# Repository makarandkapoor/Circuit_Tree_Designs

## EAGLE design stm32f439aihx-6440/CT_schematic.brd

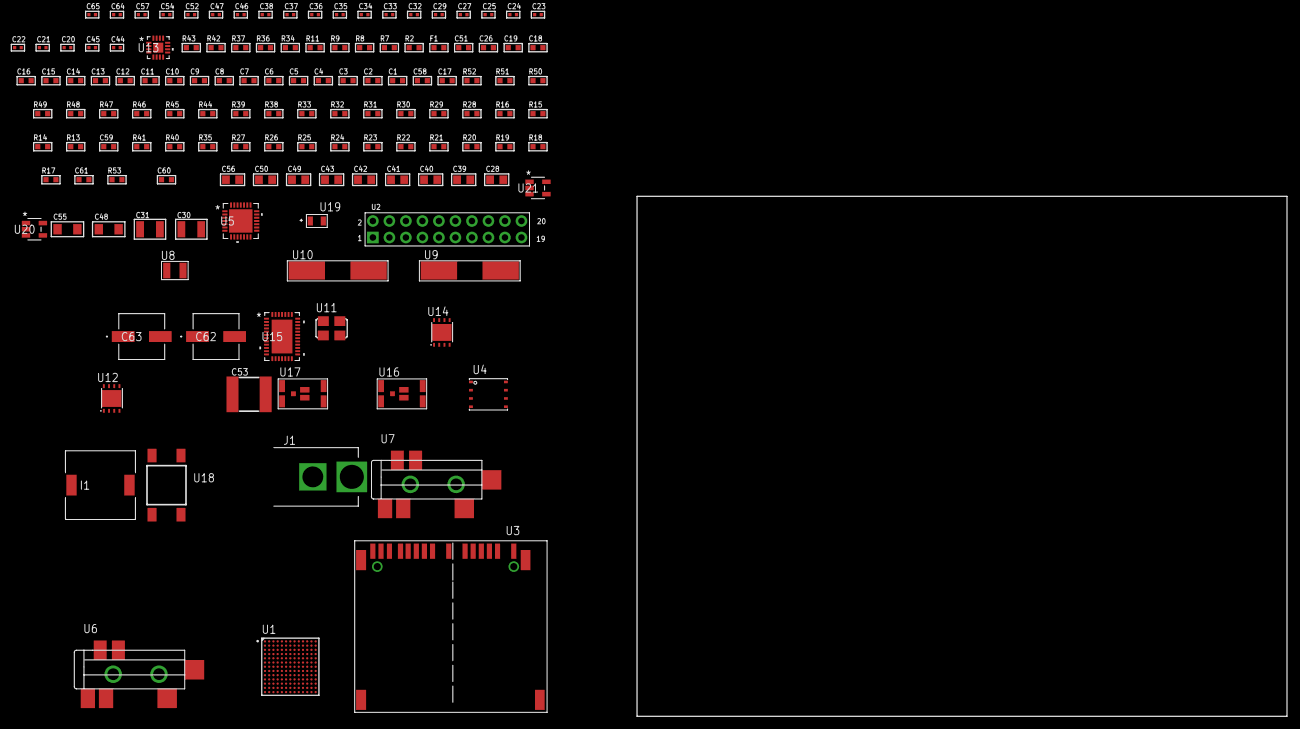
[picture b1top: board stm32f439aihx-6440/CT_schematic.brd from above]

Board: 2 copper layers, 100.0 x 80.0 mm, 135 parts (0 on the bottom side), 88 nets, no tracks yet.

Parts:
C1, C19, C26, C51: 1e-06; C0603
C2, C3, C4, C5, C6, C7, C8, C9, C10, C11, C12, C13, C14, C15, C16: 1e-07; C0603
C17: 4.7e-06; C0603
C18: 1e-08; C0603
C20, C21, C27, C34, C35, C36, C37, C38, C52, C57: 1e-07; C0402
C22, C23, C24, C25: 1e-11; C0402
C28, C39, C40, C41, C42, C43, C49, C50, C56: 1e-05; C0805
C29, C46, C47, C54, C64, C65: 1e-08; C0402
C30, C31: 2.2e-05; C1210
C32, C33: 1e-09; C0402
C44, C45: 2.2e-11; C0402
C48, C55: 1e-05; C1206
C53: 6.8e-05; 2220
C58: 2.2e-06; C0603
C59: 2.45e-08; R0603
C60: 2.8258362168397e-09; R0603
C61: 7.105e-09; R0603
C62, C63: 0.0001; EXV-9H
F1: 240.0; L0603
I1: 3.8e-06; DR1040
J1: PJ-037B; PJ-037B_PACKAGE
R2, R37, R43: 1000.0; R0603
R7, R8: 4700.0; R0603
R9, R11: 2200.0; R0603
R13, R14, R15, R16, R28, R29, R30, R44, R46, R47, R50, R51, R52: 10000.0; R0603
R17, R18, R19, R20, R21, R22, R23, R24, R25, R26, R27, R35, R41: 100000.0; R0603
R31, R32, R33: 47000.0; R0603
R34: 680.0; R0603
R36, R42: 200.0; R0603
R38: 20000.0; R0603
R39: 91000.0; R0603
R40: 300000.0; R0603
R45: 75000.0; R0603
R48, R49: 95300.0; R0603
R53: 76618.181818182; R0603
U1: STM32F439AIH6; UFBGA169
U2: arducam_ov2640; ARDUCAM
U3: 10100565
U4: 24AA256-I/MF; DFN8-S
U5: WM8731CLSEFL; QFN-28
U6, U7: SJ-43515TS-SMT-TR
U8: ABS07-32.768KHZ-7-T
U9: ABLS-25.000MHZ-B2F-T
U10: ABLS-12.288MHZ-B4-T
U11: ASFL1-25MHZ-NCS; ASFL1
U12, U14: LP3878SDX-ADJ/NOPB; WSON-8
U13: LTC3601EUD#PBF; QFN-16_EP
U15: LTC2928CUHF#PBF; QFN-38_UHF
U16, U17: IRF8306MTRPbF; IRF8306MTRPBF
U18: 4-1437565-2; SW_4-1437565-2
U19: Q65110A2395; LGM67K-G1J2-24-Z
U20, U21: nc7sz125m5x; NC7SZ125M5X

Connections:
CLK_CRYSTAL_U1_E1: C22.1, U1.E1, U8.1
CLK_CRYSTAL_U1_F1: C23.1, U1.F1, U8.2
CLK_CRYSTAL_U1_G1: C24.1, U1.G1, U9.1
CLK_CRYSTAL_U1_G2: C25.1, U1.G2, U9.2
CLK_CRYSTAL_U5_1: C44.1, U5.1, U10.1
CLK_CRYSTAL_U5_2: C45.1, U5.2, U10.2
CLK_U2_8: U2.8, U11.3
GND: C1.2, C2.2, C3.2, C4.2, C5.2, C6.2, C7.2, C8.2, C9.2, C10.2, C11.2, C12.2, C13.2, C14.2, C15.2, C16.2, C17.2, C18.2, C19.2, C20.2, C21.2, C22.2, C23.2, C24.2, C25.2, C26.2, C27.2, C28.2, C29.2, C33.2, C34.2, C35.2, C36.2, C37.2, C38.2, C39.2, C40.2, C41.2, C42.2, C43.2, C44.2, C45.2, C46.2, C47.2, C48.2, C49.2, C50.2, C51.2, C53.1, C53.2, C54.2, C55.2, C56.2, C57.2, C58.2, C59.2, C60.2, C61.2, C62.2, C63.2, C64.2, C65.2, J1.2, R2.2, R15.2, R29.2, R30.2, R31.2, R32.2, R33.2, R37.2, R38.2, R40.2, R43.2, R45.2, R48.2, R49.2, R50.2, R51.2, R52.2, U1.D7, U1.D11, U1.E7, U1.F5, U1.F6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
NET_U1_A5: R14.1, U1.A5
NET_U1_B5: R11.1, U1.B5, U4.5
NET_U1_C3: R13.1, U1.C3
NET_U1_C5: R9.1, U1.C5, U4.6
NET_U1_D12: C21.1, U1.D12
NET_U1_H2: R7.1, U1.H2, U20.4
NET_U1_J4: C18.1, C19.1, F1.1, U1.J3, U1.J4
NET_U1_L5: R15.1, U1.L5
NET_U1_M1: R16.1, U1.M1
NET_U1_N12: U18.3, U18.4
NET_U2_19: R8.1, U2.19, U21.4
NET_U3_1: R19.1, U3.1
NET_U3_2: R18.1, U3.2
NET_U3_18: U3.18, U3.19
NET_U4_1: R28.1, U4.1
NET_U4_2: R29.1, U4.2
NET_U4_3: R30.1, U4.3
NET_U5_20: C38.1, C43.1, U5.20
NET_U6_2: C31.1, R32.1, U6.2
NET_U6_5: C30.1, R31.1, U6.5
NET_U7_5: C32.1, C33.1, R33.1, R34.1, U7.5
NET_U12_1: C47.1, U12.1
NET_U12_6: R36.2, R37.1, U12.6
NET_U12_8: R35.1, U12.8
NET_U13_3: C52.2, I1.1, U13.3, U13.4
NET_U13_6: C52.1, U13.6
NET_U13_7: C51.1, U13.7, U13.12
NET_U13_10: R40.1, U13.10
NET_U13_11: R38.1, R39.1, U13.11
NET_U13_ATNET_3: I1.2, R39.2
NET_U14_1: C54.1, U14.1
NET_U14_6: R42.2, R43.1, U14.6
NET_U14_8: R41.1, U14.8
NET_U15_3: R51.1, U15.3
NET_U15_6: R48.1, U15.6
NET_U15_7: R49.1, U15.7
NET_U15_16: R50.1, R53.1, U15.16
NET_U15_18: R47.1, U15.18
NET_U15_19: R46.1, U15.19, U15.20
NET_U15_21: R44.1, R45.1, U15.21, U20.2, U21.2
NET_U15_22: C57.1, R44.2, R46.2, R47.2, U15.11, U15.22
NET_U15_26: C60.1, U15.26
NET_U15_27: C59.1, U15.27
NET_U15_28: C61.1, U15.28
NET_U15_38: R52.1, U15.38
NET_U16_3: U15.2, U16.3
NET_U17_3: U15.37, U17.3
NET_U18_1: R2.1, U18.1, U18.2
PROC_DCMI_D0: U1.E8, U2.18
PROC_DCMI_D1: U1.E9, U2.17
PROC_DCMI_D2: U1.B4, U2.16
PROC_DCMI_D3: U1.A4, U2.15
PROC_DCMI_D4: U1.C2, U2.14
PROC_DCMI_D5: U1.A9, U2.13
PROC_DCMI_D6: U1.A2, U2.12
PROC_DCMI_D7: U1.B1, U2.11
PROC_DCMI_D8: U1.C11, U2.10
PROC_DCMI_D9: U1.B12, U2.9
PROC_DCMI_HSYNC: U1.L10, U2.6
PROC_DCMI_PIXCK: U1.N3, U2.7
PROC_DCMI_VSYNC: U1.A3, U2.5
PROC_I2S2_CK: U1.L9, U5.7
PROC_I2S2_EXT_SD: U1.H6, U5.10
PROC_I2S2_SD: U1.A12, U5.8
PROC_I2S2_WS: U1.B13, U5.9, U5.11
PROC_SDIO_CK: R17.1, U3.8
PROC_SDIO_D0: R20.1, U3.4
PROC_SDIO_D1: R21.1, U3.3
PROC_SDIO_D2: R22.1, U3.15
PROC_SDIO_D3: R23.1, U3.14
PROC_SDIO_D4: R24.1, U3.13
PROC_SDIO_D5: R25.1, U3.11
PROC_SDIO_D6: R26.1, U3.7
PROC_SDIO_D7: R27.1, U3.5
VCC_9V7: C58.1, C62.1, C63.1, J1.1, R53.2, U15.23, U16.1, U16.2, U16.6, U16.7, U17.1, U17.2, U17.6, U17.7
VCC_S1_9V7: C48.1, C50.1, R35.2, U12.4, U13.15, U13.16, U16.4, U16.5
VCC_S2_9V7: C55.1, R41.2, U14.4, U17.4, U17.5
VCC_TIER1_1V2: C20.1, C49.1, R36.1, U1.N9, U12.5
VCC_TIER1_3V3: C1.1, C2.1, C3.1, C4.1, C5.1, C6.1, C7.1, C8.1, C9.1, C10.1, C11.1, C12.1, C13.1, C14.1, C15.1, C16.1, C17.1, C26.1, C27.1, C28.1, C29.1, C34.1, C35.1, C36.1, C37.1, C39.1, C40.1, C41.1, C42.1, C46.1, C53.2, C64.1, C65.1, F1.2, I1.2, R7.2, R8.2, R9.2, R11.2, R13.2, R14.2, R16.2, R17.2, R18.2, R19.2, R20.2, R21.2, R22.2, R23.2, R24.2, R25.2, R26.2, R27.2, R28.2, R39.2, U1.D3, U1.D6, U1.D10, U1.E5, U1.E6, U1.F4, U1.F7, U1.F8, U1.G8, U1.G10, U1.H4, U1.H8, U1.J11, U1.K6, U1.L6, U2.1, U3.9, U4.8, U5.3, U5.5, U5.12, U5.18, U11.4, U13.8, U20.5, U21.5
VCC_TIER2_1V2: C56.1, R42.1, U14.5

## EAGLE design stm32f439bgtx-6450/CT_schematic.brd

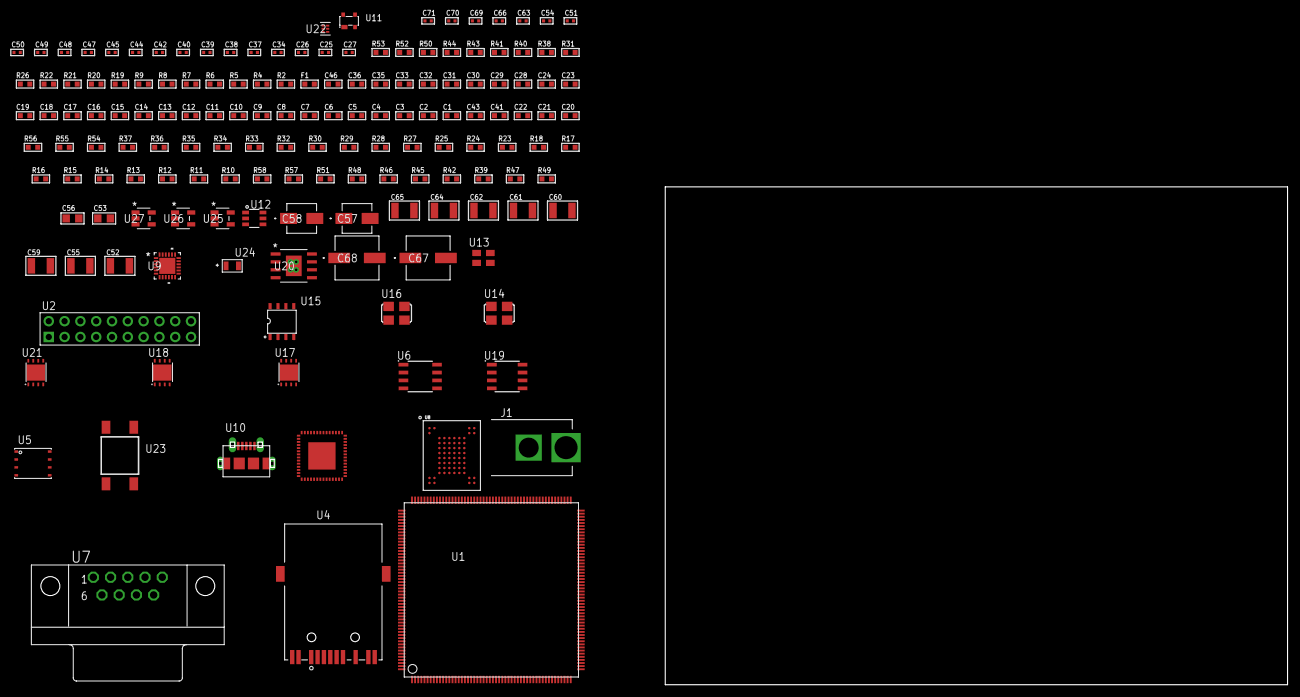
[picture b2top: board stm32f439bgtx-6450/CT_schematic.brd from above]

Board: 2 copper layers, 156 parts (0 on the bottom side), 105 nets, no tracks yet.

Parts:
C1, C24, C35, C36, C46: 1e-06; C0603
C2, C3, C4, C5, C6, C7, C8, C9, C10, C11, C12, C13, C14, C15, C16, C17, C18, C19, C28, C29, C30, C31, C32, C33: 1e-07; C0603
C20: 4.7e-06; C0603
C21, C22, C41, C43: 2.2e-06; C0603
C23: 1e-08; C0603
C25, C26, C37, C38, C39, C40, C66: 1e-07; C0402
C27: 2.2e-08; C0402
C34, C42, C44, C45, C47, C48, C49, C50, C51, C54, C63, C69, C70, C71: 1e-08; C0402
C52, C55, C59, C60, C61, C62, C64, C65: 1e-05; C1210
C53, C56: 1e-05; C0805
C57: 1e-06; EXV-9B
C58: 2.2e-06; EXV-9B
C67, C68: 0.0001; EXV-9H
F1: 240.0; L0603
J1: PJ-037B; PJ-037B_PACKAGE
R2, R41, R44, R53: 1000.0; R0603
R4, R5: 4700.0; R0603
R6, R7, R8, R9, R50: 2200.0; R0603
R10, R11, R12, R13, R14, R15, R16, R17, R18, R23, R24, R25, R27, R28, R29, R30, R32, R33, R34, R35, R36, R54, R55: 10000.0; R0603
R19, R20: 0.1; R0603
R21, R22, R40: 200.0; R0603
R26: 2000.0; R0603
R31: 120.0; R0603
R37: 47000.0; R0603
R38: 8060.0; R0603
R39, R42, R45, R46, R48, R51: 100000.0; R0603
R43: 806.0; R0603
R47: 101022.32; R0603
R49: 4031.5447154472; R0603
R52: 3900.0; R0603
R56: 82000.0; R0603
R57: 300000.0; R0603
R58: 120000.0; R0603
U1: STM32F439BGT6; LQFP208
U2: TST-110-05-T-D-RA
U3: 88E3015A2NNP1C000
U4: 7498011122R
U5: 24AA512-I/MF; DFN8-S
U6: MCP2562-E/SN; SOIC-8
U7: 182-009-113R531; 182-009-MALE
U8: mt29f4g08abbdah4; VFBGA-63
U9: USB3317C-CP-TR; QFN-24
U10: 47590-0001; MICRO_USB_AB
U11: prtr5v0u2ax; SOT143B
U12: MAX4995AAUT+T; SOT-23-6
U13: ASEK-32.768KHz-ECST; ASEK
U14: ASFL1-25MHZ-NCS; ASFL1
U15: idt74fct38072; IDT74FCT38072
U16: ASFL1-26MHZ-NCS; ASFL1
U17, U18, U21: LP3878SDX-ADJ/NOPB; WSON-8
U19: LP2954AIMX/NOPB; LP2954
U20: MIC5234YME; SOIC-8_EP
U22: TPS3895ADRYR; SON-6
U23: 4-1437565-2; SW_4-1437565-2
U24: Q65110A2395; LGM67K-G1J2-24-Z
U25, U26, U27: nc7sz125m5x; NC7SZ125M5X

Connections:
CLK_U1_9: U1.9, U13.3
CLK_U1_32: U1.32, U15.7
CLK_U3_32: U3.32, U15.6
CLK_U9_23: U9.23, U16.3
CLK_U15_3: U14.3, U15.3
GND: C1.2, C2.2, C3.2, C4.2, C5.2, C6.2, C7.2, C8.2, C9.2, C10.2, C11.2, C12.2, C13.2, C14.2, C15.2, C16.2, C17.2, C18.2, C19.2, C20.2, C21.2, C22.2, C23.2, C24.2, C25.2, C26.2, C27.2, C28.2, C29.2, C30.2, C31.2, C32.2, C33.2, C34.2, C35.2, C36.2, C37.2, C38.2, C39.2, C40.2, C41.2, C42.2, C43.2, C44.2, C45.2, C46.2, C47.2, C48.2, C49.2, C50.2, C51.2, C52.2, C53.2, C54.2, C55.2, C56.2, C57.2, C58.2, C59.2, C60.2, C61.2, C62.2, C63.2, C64.2, C65.2, C66.2, C67.2, C68.2, C69.2, C70.2, C71.2, J1.2, R2.2, R12.2, R18.2, R19.2, R20.2, R26.2, R27.2, R29.2, R37.2, R38.2, R41.2, R44.2, R48.2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
NET_U1_34: R4.1, U1.34, U26.4
NET_U1_42: C23.1, C24.1, F1.1, U1.41, U1.42
NET_U1_63: R12.1, U1.63
NET_U1_92: C21.1, U1.92
NET_U1_148: C22.1, U1.148
NET_U1_195: R6.1, U1.195, U5.6
NET_U1_196: R7.1, U1.196, U5.5
NET_U1_197: R11.1, U1.197
NET_U1_203: R10.1, U1.203
NET_U1_208: U23.3, U23.4
NET_U2_19: R18.1, U2.19
NET_U3_9: R24.1, U3.9
NET_U3_10: R27.1, U3.10
NET_U3_16: R23.1, U3.16
NET_U3_28: R26.1, U3.28
NET_U3_39: R25.1, U3.39
NET_U3_44: U3.44, U3.48, U3.49, U3.56
NET_U4_1: U3.26, U4.1
NET_U4_3: U3.25, U4.3
NET_U4_4: U3.23, U4.4
NET_U4_5: C27.1, U4.2, U4.5
NET_U4_6: U3.22, U4.6
NET_U4_8: R20.1, R22.2, U4.8
NET_U4_9: R21.1, U4.9
NET_U4_11: R22.1, U4.11
NET_U4_13: R19.1, U4.13, U4.14
NET_U5_1: R28.1, U5.1
NET_U5_2: R29.1, U5.2
NET_U5_3: R30.1, U5.3
NET_U6_6: R31.2, U6.6
NET_U7_2: R31.2, U6.6, U7.2
NET_U7_3: R31.1, U6.7, U7.3
NET_U8_C3: R36.1, U8.C3
NET_U9_4: C43.1, U9.4
NET_U9_22: R5.1, U9.22, U27.4
NET_U9_24: R38.1, U9.24
NET_U10_1: C46.1, U9.2, U10.1, U11.4, U12.1
NET_U10_2: U9.5, U10.2, U11.3
NET_U10_3: U9.6, U10.3, U11.2
NET_U10_4: U9.1, U10.4
NET_U12_3: R37.1, U12.3
NET_U12_4: U9.7, U12.4
NET_U17_1: C51.1, U17.1
NET_U17_6: R40.2, R41.1, U17.6
NET_U17_8: R39.1, U17.8
NET_U18_1: C54.1, U18.1
NET_U18_6: R43.2, R44.1, U18.6
NET_U18_8: R42.1, U18.8
NET_U19_3: R46.1, U19.3
NET_U19_5: R45.1, U19.5
NET_U19_7: R47.2, R48.1, U19.7
NET_U20_4: R49.2, R50.1, U20.4
NET_U21_1: C63.1, U21.1
NET_U21_6: R52.2, R53.1, U21.6
NET_U21_8: R51.1, U21.8
NET_U22_1: R55.1, R56.1, U22.1
NET_U22_3: R57.2, R58.1, U22.3
NET_U22_4: R54.1, U22.4, U25.4, U26.2, U27.2
NET_U23_1: R2.1, U23.1, U23.2
PROC_CAN1_RX: U1.11, U6.4
PROC_CAN1_TX: U1.146, U6.1
PROC_FMC_A16: U1.111, U8.D5
PROC_FMC_A17: U1.112, U8.C4
PROC_FMC_D0: U1.116, U8.H4
PROC_FMC_D1: U1.117, U8.J4
PROC_FMC_D2: U1.164, U8.K4
PROC_FMC_D3: U1.165, U8.K5
PROC_FMC_D4: U1.79, U8.K6
PROC_FMC_D5: U1.80, U8.J7
PROC_FMC_D6: U1.81, U8.K7
PROC_FMC_D7: U1.84, U8.J8
PROC_FMC_INT2: R32.1, U1.133, U8.C8
PROC_FMC_NCE2: R33.1, U1.173, U8.C6
PROC_FMC_NOE: R35.1, U1.168, U8.D4
PROC_FMC_NWE: R34.1, U1.169, U8.C7
PROC_SYS_JTCK_SWCLK: R16.1, U1.159, U2.9
PROC_SYS_JTDI: R14.1, U1.160, U2.5
PROC_SYS_JTDO_SWO: U1.192, U2.13
PROC_SYS_JTMS_SWDIO: R15.1, U1.147, U2.7
PROC_SYS_JTRST: R13.1, U1.193, U2.3
PROC_USB_OTG_HS_ULPI_CK: U1.54, U9.12
PROC_USB_OTG_HS_ULPI_D0: U1.50, U9.16
PROC_USB_OTG_HS_ULPI_D1: U1.61, U9.15
PROC_USB_OTG_HS_ULPI_D2: U1.62, U9.14
PROC_USB_OTG_HS_ULPI_D3: U1.90, U9.13
PROC_USB_OTG_HS_ULPI_D4: U1.91, U9.11
PROC_USB_OTG_HS_ULPI_D5: U1.104, U9.10
PROC_USB_OTG_HS_ULPI_D6: U1.105, U9.9
PROC_USB_OTG_HS_ULPI_D7: U1.194, U9.8
PROC_USB_OTG_HS_ULPI_DIR: U1.13, U9.19
PROC_USB_OTG_HS_ULPI_NXT: U1.48, U9.18
PROC_USB_OTG_HS_ULPI_STP: U1.35, U9.20
RST_OUT_U2_SRESET_B: R17.1, U2.15, U25.1
VCC_S1_12V4: C52.1, C55.1, C57.1, C59.1, C60.1, C64.1, C67.1, C68.1, J1.1, R39.2, R42.2, R46.2, R51.2, U17.4, U18.4, U19.8, U20.5, U20.8, U21.4
VCC_TIER1_1V2: C53.1, R40.1, U17.5
VCC_TIER1_1V8: C1.1, C2.1, C3.1, C4.1, C5.1, C6.1, C7.1, C8.1, C9.1, C10.1, C11.1, C12.1, C13.1, C14.1, C15.1, C16.1, C17.1, C18.1, C19.1, C20.1, C26.1, C34.1, C36.1, C37.1, C38.1, C39.1, C40.1, C41.1, C44.1, C45.1, C56.1, C66.1, C69.1, C70.1, C71.1, F1.2, R4.2, R5.2, R6.2, R7.2, R8.2, R9.2, R10.2, R11.2, R13.2, R14.2, R15.2, R16.2, R17.2, R28.2, R30.2, R32.2, R33.2, R34.2, R35.2, R36.2, R43.1, R54.2, R55.2, R57.1, U1.6, U1.15, U1.26, U1.39, U1.52, U1.59, U1.73, U1.83, U1.94, U1.103, U1.115, U1.124, U1.137, U1.150, U1.158, U1.171, U1.185, U1.204, U2.1, U5.8, U6.5, U8.D3, U8.G4, U8.H8, U8.J6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
VCC_TIER1_2V5: C28.1, C29.1, C30.1, C31.1, C32.1, C33.1, C58.1, R23.2, R24.2, R25.2, R45.2, R47.1, U3.4, U3.6, U3.11, U3.12, U3.13, U3.20, U3.24, U3.29, U3.34, U3.36, U4.2, U19.1
VCC_TIER1_3V3: C25.1, C42.1, C47.1, C48.1, C49.1, C50.1, C61.1, C62.1, R49.1, U2.2, U9.3, U13.4, U14.4, U15.1, U15.2, U16.4, U20.1
VCC_TIER1_5V0: C35.1, C65.1, R52.1, U6.3, U12.5, U21.5

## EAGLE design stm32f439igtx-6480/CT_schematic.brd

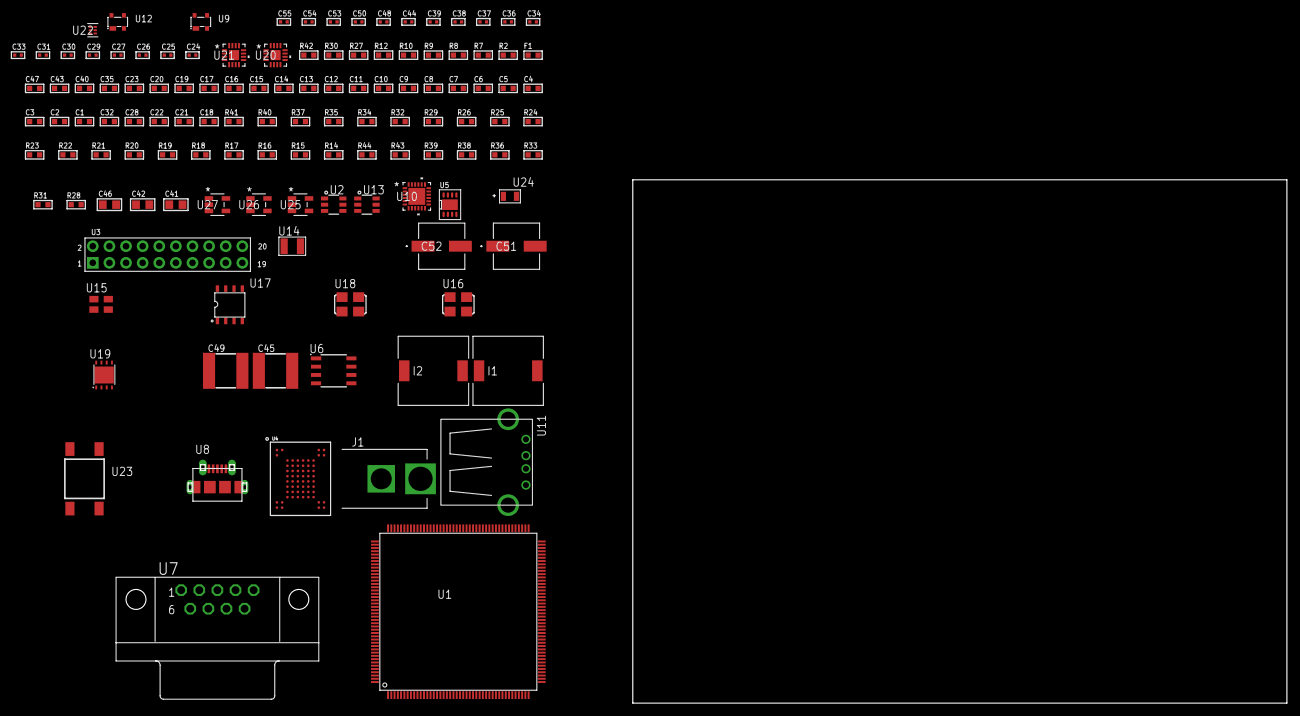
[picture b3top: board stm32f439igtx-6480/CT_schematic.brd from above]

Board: 2 copper layers, 123 parts (0 on the bottom side), 103 nets, no tracks yet.

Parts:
C1, C20, C23, C40, C43, C47: 1e-06; C0603
C2, C3, C4, C5, C6, C7, C8, C9, C10, C11, C12, C13, C14, C15, C16, C17: 1e-07; C0603
C18: 4.7e-06; C0603
C19: 1e-08; C0603
C21, C22, C28, C32: 2.2e-06; C0603
C24, C25, C26, C27, C29, C30, C44, C48, C50: 1e-07; C0402
C31, C33, C34, C36, C37, C38, C39, C53, C54, C55: 1e-08; C0402
C35: 0.0001; R0603
C41, C42, C46: 1e-05; C0805
C45, C49: 6.8e-05; 2220
C51, C52: 0.0001; EXV-9H
F1: 240.0; L0603
I1, I2: 2.5e-06; DR1040
J1: PJ-037B; PJ-037B_PACKAGE
R2: 1000.0; R0603
R7, R8, R9: 4700.0; R0603
R10, R12: 2200.0; R0603
R14, R29: 47000.0; R0603
R15, R16, R17, R18, R19, R20, R21, R22, R23, R24, R25, R26, R40, R41: 10000.0; R0603
R27: 120.0; R0603
R28: 470000.0; R0603
R30: 8060.0; R0603
R31, R33: 100000.0; R0603
R32: 36000.0; R0603
R34, R37: 20000.0; R0603
R35: 91000.0; R0603
R36, R39: 300000.0; R0603
R38: 150000.0; R0603
R42: 9100.0; R0603
R43: 680000.0; R0603
R44: 120000.0; R0603
U1: STM32F439IGT6; LQFP176
U2, U13: MAX4995AAUT+T; SOT-23-6
U3: arducam_ov2640; ARDUCAM
U4: mt29f4g08abadah4; VFBGA-63
U5: PCF85063TP/1Z; SON-8
U6: SN65HVD230D; SOIC-8
U7: 182-009-113R531; 182-009-MALE
U8: 47590-0001; MICRO_USB_AB
U9, U12: prtr5v0u2ax; SOT143B
U10: USB3317C-CP-TR; QFN-24
U11: 61400416021; USB-A-H
U14: ABS07-32.768KHZ-7-T
U15: ASEK-32.768KHz-ECST; ASEK
U16: ASFL1-25MHZ-NCS; ASFL1
U17: idt74fct38072; IDT74FCT38072
U18: ASFL1-26MHZ-NCS; ASFL1
U19: LP2951ACSDX/NOPB; WSON-8
U20, U21: LTC3601EUD#PBF; QFN-16_EP
U22: TPS3895ADRYR; SON-6
U23: 4-1437565-2; SW_4-1437565-2
U24: Q65110A2395; LGM67K-G1J2-24-Z
U25, U26, U27: nc7sz125m5x; NC7SZ125M5X

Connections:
CLK_CRYSTAL_U5_1: U5.1, U14.1
CLK_CRYSTAL_U5_2: U5.2, U14.2
CLK_U1_9: U1.9, U15.3
CLK_U1_29: U1.29, U17.6
CLK_U3_8: U3.8, U17.7
CLK_U10_23: U10.23, U18.3
CLK_U17_3: U16.3, U17.3
GND: C1.2, C2.2, C3.2, C4.2, C5.2, C6.2, C7.2, C8.2, C9.2, C10.2, C11.2, C12.2, C13.2, C14.2, C15.2, C16.2, C17.2, C18.2, C19.2, C20.2, C21.2, C22.2, C23.2, C24.2, C25.2, C26.2, C27.2, C28.2, C29.2, C30.2, C31.2, C32.2, C33.2, C34.2, C35.2, C36.2, C37.2, C38.2, C39.2, C40.2, C41.2, C42.2, C43.2, C45.1, C45.2, C46.2, C47.2, C49.1, C49.2, C50.2, C51.2, C52.2, C53.2, C54.2, C55.2, J1.2, R2.2, R14.2, R18.2, R20.2, R28.2, R29.2, R30.2, R33.2, R34.2, R36.2, R37.2, R39.2, R42.2, R44.2, U1.14, U1.22, U1.37, U1.61, U1.71, U1.90, U1.102, U1.113, U1.126, U1.135, U1.148, U1.158, U2.2, U3.2, U3.20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
NET_U1_31: R7.1, U1.31, U25.4
NET_U1_39: C19.1, C20.1, F1.1, U1.38, U1.39
NET_U1_48: R18.1, U1.48
NET_U1_58: R17.1, U1.58
NET_U1_81: C21.1, U1.81
NET_U1_125: C22.1, U1.125
NET_U1_164: R10.1, U1.164, U5.6
NET_U1_165: R12.1, U1.165, U5.5
NET_U1_166: R16.1, U1.166
NET_U1_171: R15.1, U1.171
NET_U1_176: U23.3, U23.4
NET_U2_3: R14.1, U2.3
NET_U3_19: R8.1, U3.19, U26.4
NET_U4_C3: R25.1, U4.C3
NET_U5_3: R26.1, U5.3
NET_U6_6: R27.2, U6.6
NET_U6_8: R28.1, U6.8
NET_U7_2: R27.2, U6.6, U7.2
NET_U7_3: R27.1, U6.7, U7.3
NET_U10_4: C32.1, U10.4
NET_U10_22: R9.1, U10.22, U27.4
NET_U10_24: R30.1, U10.24
NET_U11_1: C35.1, U10.2, U11.1, U12.4, U13.1
NET_U11_2: U10.5, U11.2, U12.3
NET_U11_3: U10.6, U11.3, U12.2
NET_U13_3: R29.1, U13.3
NET_U13_4: U10.7, U13.4
NET_U19_5: R31.1, U19.5
NET_U19_7: R32.2, R33.1, U19.7
NET_U20_3: C44.2, I1.1, U20.3, U20.4
NET_U20_6: C44.1, U20.6
NET_U20_7: C43.1, U20.7, U20.12
NET_U20_10: R36.1, U20.10
NET_U20_11: R34.1, R35.1, U20.11
NET_U20_ATNET_3: I1.2, R35.2
NET_U21_3: C48.2, I2.1, U21.3, U21.4
NET_U21_6: C48.1, U21.6
NET_U21_7: C47.1, U21.7, U21.12
NET_U21_10: R39.1, U21.10
NET_U21_11: R37.1, R38.1, U21.11
NET_U21_ATNET_3: I2.2, R38.2
NET_U22_1: R41.1, R42.1, U22.1
NET_U22_3: R43.2, R44.1, U22.3
NET_U22_4: R40.1, U22.4, U25.2, U26.2, U27.2
NET_U23_1: R2.1, U23.1, U23.2
PROC_CAN1_RX: U1.11, U6.4
PROC_CAN1_TX: U1.128, U6.1
PROC_DCMI_D0: U1.86, U3.18
PROC_DCMI_D1: U1.87, U3.17
PROC_DCMI_D2: U1.88, U3.16
PROC_DCMI_D3: U1.89, U3.15
PROC_DCMI_D4: U1.3, U3.14
PROC_DCMI_D5: U1.145, U3.13
PROC_DCMI_D6: U1.4, U3.12
PROC_DCMI_D7: U1.5, U3.11
PROC_DCMI_D8: U1.83, U3.10
PROC_DCMI_D9: U1.84, U3.9
PROC_DCMI_HSYNC: U1.50, U3.6
PROC_DCMI_PIXCK: U1.52, U3.7
PROC_DCMI_VSYNC: U1.152, U3.5
PROC_FMC_A16: U1.99, U4.D5
PROC_FMC_A17: U1.100, U4.C4
PROC_FMC_D0: U1.104, U4.H4
PROC_FMC_D1: U1.105, U4.J4
PROC_FMC_D2: U1.142, U4.K4
PROC_FMC_D3: U1.143, U4.K5
PROC_FMC_D4: U1.68, U4.K6
PROC_FMC_D5: U1.69, U4.J7
PROC_FMC_D6: U1.70, U4.K7
PROC_FMC_D7: U1.73, U4.J8
PROC_FMC_INT2: R21.1, U1.110, U4.C8
PROC_FMC_NCE2: R22.1, U1.151, U4.C6
PROC_FMC_NOE: R24.1, U1.146, U4.D4
PROC_FMC_NWE: R23.1, U1.147, U4.C7
PROC_GPIO_TO_U1_USB_FAULT: R19.1, U1.2, U2.6
PROC_GPIO_TO_U1_VBUS_EN: R20.1, U1.1, U2.4
PROC_USB_OTG_FS_DM: U8.2, U9.3
PROC_USB_OTG_FS_DP: U8.3, U9.2
PROC_USB_OTG_FS_VBUS: U2.1, U8.1, U9.4
PROC_USB_OTG_HS_ULPI_CK: U1.51, U10.12
PROC_USB_OTG_HS_ULPI_D0: U1.47, U10.16
PROC_USB_OTG_HS_ULPI_D1: U1.56, U10.15
PROC_USB_OTG_HS_ULPI_D2: U1.57, U10.14
PROC_USB_OTG_HS_ULPI_D3: U1.79, U10.13
PROC_USB_OTG_HS_ULPI_D4: U1.80, U10.11
PROC_USB_OTG_HS_ULPI_D5: U1.92, U10.10
PROC_USB_OTG_HS_ULPI_D6: U1.93, U10.9
PROC_USB_OTG_HS_ULPI_D7: U1.163, U10.8
PROC_USB_OTG_HS_ULPI_DIR: U1.13, U10.19
PROC_USB_OTG_HS_ULPI_NXT: U1.35, U10.18
PROC_USB_OTG_HS_ULPI_STP: U1.32, U10.20
VCC_S1_6V6: C40.1, C42.1, C46.1, C51.1, C52.1, J1.1, U19.8, U20.15, U20.16, U21.15, U21.16
VCC_TIER1_1V8: C34.1, C41.1, C53.1, C54.1, C55.1, R31.2, R32.1, U10.21, U19.1, U25.5, U26.5, U27.5
VCC_TIER1_3V3: C1.1, C2.1, C3.1, C4.1, C5.1, C6.1, C7.1, C8.1, C9.1, C10.1, C11.1, C12.1, C13.1, C14.1, C15.1, C16.1, C17.1, C18.1, C23.1, C24.1, C25.1, C26.1, C27.1, C28.1, C29.1, C30.1, C31.1, C33.1, C36.1, C37.1, C38.1, C39.1, C45.2, C50.1, F1.2, I1.2, R7.2, R8.2, R9.2, R10.2, R12.2, R15.2, R16.2, R17.2, R19.2, R21.2, R22.2, R23.2, R24.2, R25.2, R26.2, R35.2, R40.2, R41.2, R43.1, U1.6, U1.15, U1.23, U1.36, U1.49, U1.62, U1.72, U1.82, U1.91, U1.103, U1.114, U1.127, U1.136, U1.149, U1.159, U1.172, U3.1, U4.D3, U4.G4, U4.H8, U4.J6, U5.8, U6.3, U10.3, U10.17, U15.4, U16.4, U17.1, U17.2, U18.4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
VCC_TIER1_5V0: C49.2, I2.2, R38.2, U2.5, U13.5, U21.8

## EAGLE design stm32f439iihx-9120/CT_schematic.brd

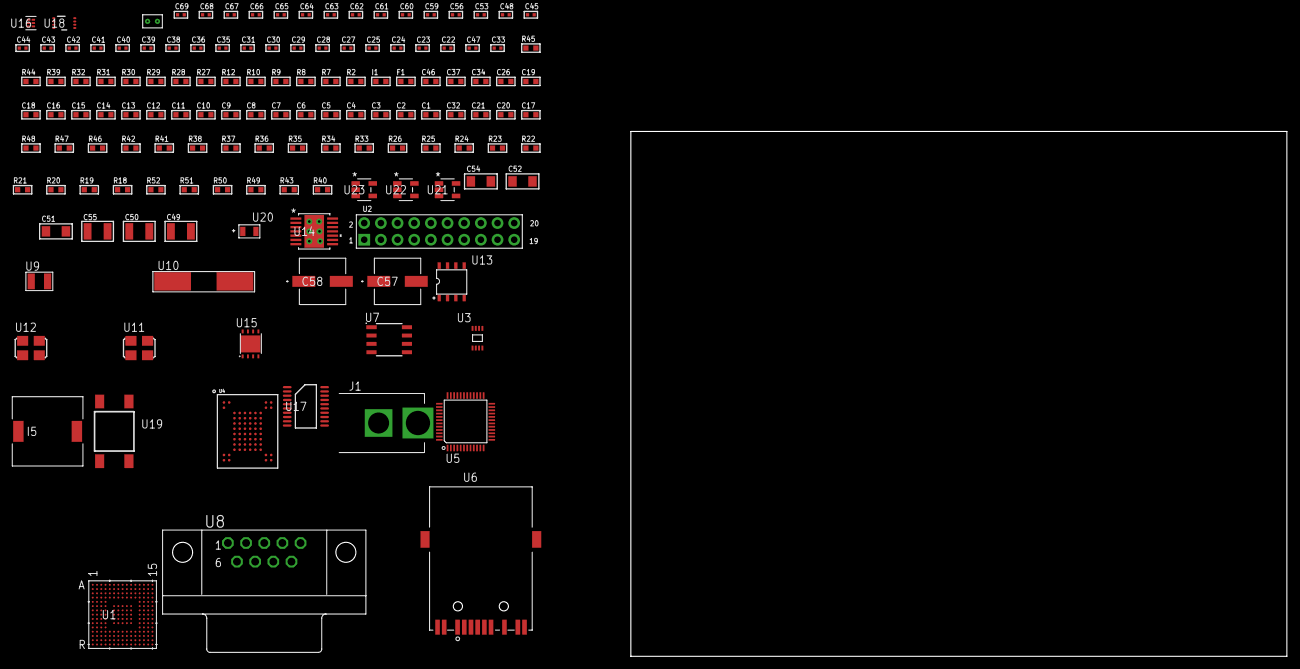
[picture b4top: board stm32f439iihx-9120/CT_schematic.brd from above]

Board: 2 copper layers, 100.0 x 80.0 mm, 138 parts (0 on the bottom side), 89 nets, no tracks yet.

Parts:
C1, C19, C26, C34, C37, C46: 1e-06; C0603
C2, C3, C4, C5, C6, C7, C8, C9, C10, C11, C12, C13, C14, C15, C16: 1e-07; C0603
C17: 4.7e-06; C0603
C18: 1e-08; C0603
C20, C21, C32: 2.2e-06; C0603
C22, C23, C24, C25: 1e-11; C0402
C27, C36, C39, C43, C44, C45, C53, C59, C61, C63, C65, C67, C68, C69: 1e-08; C0402
C28, C29, C30, C31, C35, C38, C40, C41, C42, C48, C56, C60, C62, C64, C66: 1e-07; C0402
C33: 2.2e-08; C0402
C47: 3.3e-09; C0402
C49, C50: 2.2e-05; C1210
C51, C52, C54: 1e-05; C1206
C55: 1e-05; C1210
C57, C58: 0.0001; EXV-9H
F1: 240.0; L0603
I1: 97.0; R0603
I5: 2.5e-06; DR1040
J1: PJ-037B; PJ-037B_PACKAGE
R2, R45: 1000.0; R0603
R7, R8, R9, R32: 4700.0; R0603
R10, R12: 2200.0; R0603
R18, R19, R20, R21, R22, R23, R24, R25, R26, R33, R34, R35, R36, R37, R38, R46, R47: 10000.0; R0603
R27, R28: 0.1; R0603
R29, R30: 200.0; R0603
R31: 2490.0; R0603
R39: 120.0; R0603
R40, R43: 100000.0; R0603
R41: 30000.0; R0603
R42: 22000.0; R0603
R44: 2231.0; R0603
R48: 82000.0; R0603
R49: 300000.0; R0603
R50: 120000.0; R0603
R51, R52: 200000.0; R0603
U1: STM32F439IIH7; UFBGA176_25
U2: arducam_ov2640; ARDUCAM
U3: 24AA01T-I/MNY; TDFN-8/6MM
U4: mt29f4g08abbdah4; VFBGA-63
U5: RTL8201FL-VB-CG
U6: 7498011122R
U7: SN65HVD230D; SOIC-8
U8: 182-009-113R531; 182-009-MALE
U9: ABS07-32.768KHZ-7-T
U10: ABLS-25.000MHZ-B2F-T
U11: ASFL1-25MHZ-NCS; ASFL1
U12: ASFL1-50MHZ-NCS; ASFL1
U13: idt74fct38072; IDT74FCT38072
U14: tps54325PWP; HTSSOP14
U15: LP3878SDX-ADJ/NOPB; WSON-8
U16: TPS3895ADRYR; SON-6
U17: LSF0108PWR; PW0020A
U18: LSF0102DCTR; DCU0008A_N
U19: 4-1437565-2; SW_4-1437565-2
U20: Q65110A2395; LGM67K-G1J2-24-Z
U21, U22, U23: nc7sz125m5x; NC7SZ125M5X
U24: Dummy; DUMMY_PACKAGE_283

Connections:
CLK_CRYSTAL_U1_E1: C22.1, U1.E1, U9.1
CLK_CRYSTAL_U1_F1: C23.1, U1.F1, U9.2
CLK_CRYSTAL_U1_G1: C24.1, U1.G1, U10.1
CLK_CRYSTAL_U1_H1: C25.1, U1.H1, U10.2
CLK_U1_N2: U1.N2, U13.7
CLK_U2_8: U2.8, U11.3
CLK_U5_43: U5.43, U13.6
CLK_U13_3: U12.3, U13.3
GND: C1.2, C2.2, C3.2, C4.2, C5.2, C6.2, C7.2, C8.2, C9.2, C10.2, C11.2, C12.2, C13.2, C14.2, C15.2, C16.2, C17.2, C18.2, C19.2, C20.2, C21.2, C22.2, C23.2, C24.2, C25.2, C26.2, C27.2, C28.2, C29.2, C30.2, C31.2, C32.2, C33.2, C34.2, C35.2, C36.2, C37.2, C38.2, C39.2, C40.2, C41.2, C42.2, C43.2, C44.2, C45.2, C46.2, C47.2, C49.2, C50.2, C51.2, C52.2, C53.2, C54.2, C55.2, C56.2, C57.2, C58.2, C59.2, C60.2, C61.2, C62.2, C63.2, C64.2, C65.2, C66.2, C67.2, C68.2, C69.2, J1.2, R2.2, R20.2, R21.2, R27.2, R28.2, R31.2, R36.2, R37.2, R40.2, R42.2, R45.2, R48.2, R50.2, U1.D5, U1.D7, U1.D8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
NET_U1_A5: R10.1, U1.A5, U3.6
NET_U1_B4: R12.1, U1.B4, U3.5
NET_U1_C6: R18.1, U1.C6
NET_U1_D6: R19.1, U1.D6
NET_U1_F13: C21.1, U1.F13
NET_U1_J1: R8.1, U1.J1, U22.4
NET_U1_L4: R21.1, U1.L4
NET_U1_M6: R20.1, U1.M6
NET_U1_M10: C20.1, U1.M10
NET_U1_R1: C18.1, C19.1, F1.1, U1.P1, U1.R1
NET_U1_R15: U19.3, U19.4
NET_U2_19: R9.1, U2.19, U23.4
NET_U4_C3: R26.1, U4.C3
NET_U5_6: C34.1, C35.1, C36.1, I1.1, U5.6, U5.41
NET_U5_10: R36.1, U5.10
NET_U5_13: R33.1, U5.13
NET_U5_18: R37.1, U5.18
NET_U5_29: R7.1, U5.29, U21.4
NET_U5_32: R32.1, U5.32
NET_U5_34: R34.1, U5.34
NET_U5_35: R35.1, U5.35
NET_U5_39: R38.1, U5.39
NET_U5_40: C41.1, U5.40
NET_U5_46: R31.1, U5.46
NET_U5_48: C40.1, U5.48
NET_U6_1: U5.1, U6.1
NET_U6_3: U5.2, U6.3
NET_U6_4: U5.4, U6.4
NET_U6_5: C33.1, U6.2, U6.5
NET_U6_6: U5.5, U6.6
NET_U6_8: R28.1, U6.8
NET_U6_10: R29.1, U6.10
NET_U6_12: R30.1, U6.12
NET_U6_13: R27.1, U6.13, U6.14
NET_U7_6: R39.2, U7.6
NET_U7_8: R40.1, U7.8
NET_U8_2: R39.2, U7.6, U8.2
NET_U8_3: R39.1, U7.7, U8.3
NET_U14_2: R41.2, R42.1, U14.2
NET_U14_3: C46.1, U14.3
NET_U14_4: C47.1, U14.4
NET_U14_10: C48.1, I5.1, U14.10, U14.11
NET_U14_12: C48.2, U14.12
NET_U15_1: C53.1, U15.1
NET_U15_6: R44.2, R45.1, U15.6
NET_U15_8: R43.1, U15.8
NET_U16_1: R47.1, R48.1, U16.1
NET_U16_3: R49.2, R50.1, U16.3
NET_U16_4: R46.1, U16.4, U21.2, U22.2, U23.2
NET_U17_20: R51.1, U17.20
NET_U18_8: R52.1, U18.8
NET_U19_1: R2.1, U19.1, U19.2
PROC_CAN1_RX_TOXCVR: U7.4, U18.5
PROC_CAN1_TX_TOXCVR: U7.1, U18.6
PROC_DAC_OUT2: U1.P4, U24.2
PROC_ETH_CRS_DV_TOXCVR: U5.36, U17.15
PROC_ETH_MDC_TOXCVR: U5.30, U17.17
PROC_ETH_MDIO_TOXCVR: U5.31, U17.18
PROC_ETH_RXD0_TOXCVR: U5.14, U17.13
PROC_ETH_RXD1_TOXCVR: U5.16, U17.11
PROC_ETH_TXD0_TOXCVR: U5.23, U17.12
PROC_ETH_TXD1_TOXCVR: U5.24, U17.16
PROC_ETH_TX_EN_TOXCVR: U5.27, U17.14
PROC_FMC_A16: U1.N14, U4.D5
PROC_FMC_A17: U1.N13, U4.C4
PROC_FMC_D0: U1.M14, U4.H4
PROC_FMC_D1: U1.L14, U4.J4
PROC_FMC_D2: U1.B12, U4.K4
PROC_FMC_D3: U1.C12, U4.K5
PROC_FMC_D4: U1.R8, U4.K6
PROC_FMC_D5: U1.P8, U4.J7
PROC_FMC_D6: U1.P9, U4.K7
PROC_FMC_D7: U1.R9, U4.J8
PROC_FMC_INT2: R22.1, U1.J15, U4.C8
PROC_FMC_NCE2: R23.1, U1.A11, U4.C6
PROC_FMC_NOE: R25.1, U1.D10, U4.D4
PROC_FMC_NWE: R24.1, U1.C11, U4.C7
VCC_S1_7V1: C51.1, C52.1, C54.1, C57.1, C58.1, J1.1, R43.2, U14.7, U14.13, U14.14, U15.4
VCC_TIER1_1V8: C1.1, C2.1, C3.1, C4.1, C5.1, C6.1, C7.1, C8.1, C9.1, C10.1, C11.1, C12.1, C13.1, C14.1, C15.1, C16.1, C17.1, C27.1, C28.1, C29.1, C30.1, C31.1, C32.1, C49.1, C50.1, C56.1, C61.1, C62.1, C65.1, C66.1, C67.1, C68.1, C69.1, F1.2, I5.2, R8.2, R10.2, R12.2, R18.2, R19.2, R22.2, R23.2, R24.2, R25.2, R26.2, R41.1, R46.2, R47.2, R49.1, U1.C1, U1.C5, U1.C7, U1.C8, U1.C9, U1.F3, U1.G3, U1.G13, U1.H13, U1.J12, U1.J13, U1.K4, U1.N8, U1.N9, U1.N10, U3.8, U4.D3, U4.G4, U4.H8, U4.J6, U14.1, U16.6, U17.2, U18.2, U21.5, U22.5, U23.5
VCC_TIER1_3V3: C26.1, C37.1, C38.1, C39.1, C42.1, C43.1, C44.1, C45.1, C55.1, C59.1, C60.1, C63.1, C64.1, I1.2, R7.2, R9.2, R32.2, R33.2, R34.2, R35.2, R38.2, R44.1, R51.2, R52.2, U2.1, U5.15, U5.21, U5.37, U6.9, U6.11, U7.3, U11.4, U12.4, U13.1, U13.2, U15.5, U17.19, U18.7

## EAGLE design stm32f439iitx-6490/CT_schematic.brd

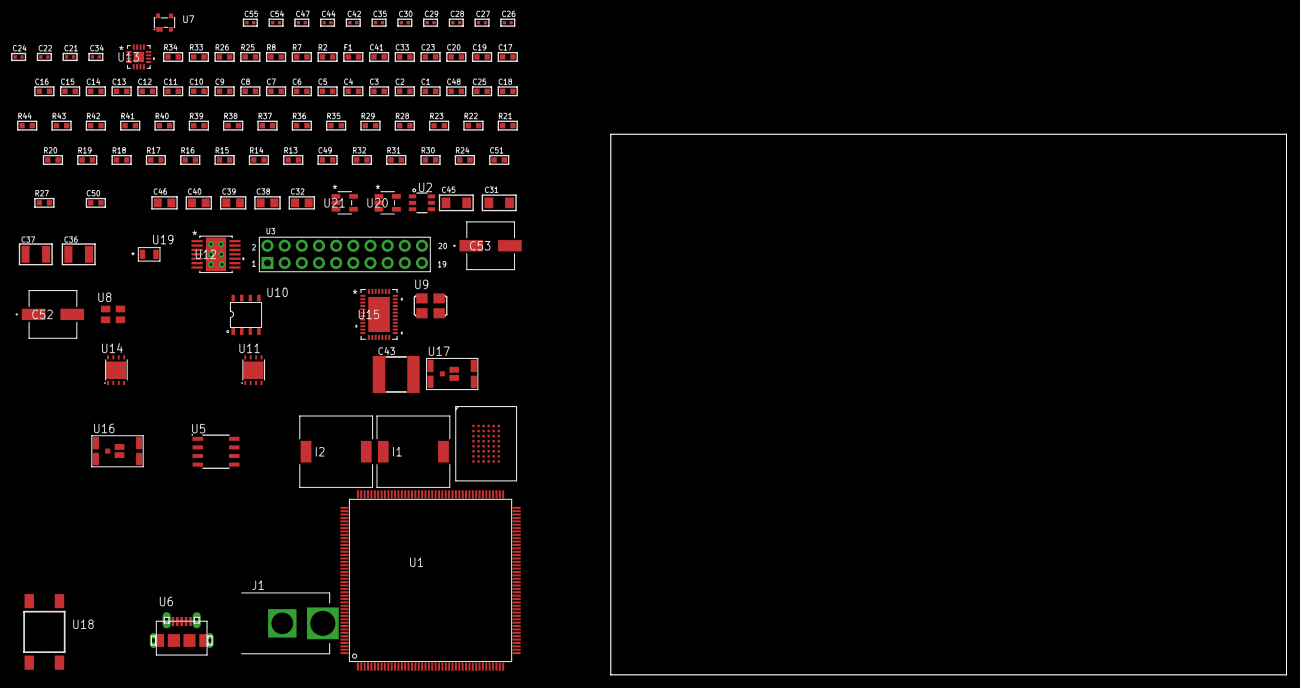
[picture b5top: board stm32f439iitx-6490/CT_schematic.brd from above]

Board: 2 copper layers, 115 parts (0 on the bottom side), 112 nets, no tracks yet.

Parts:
C1, C20, C23, C33, C41: 1e-06; C0603
C2, C3, C4, C5, C6, C7, C8, C9, C10, C11, C12, C13, C14, C15, C16, C17: 1e-07; C0603
C18: 4.7e-06; C0603
C19: 1e-08; C0603
C21, C22, C24, C35, C42, C47: 1e-07; C0402
C25, C48: 2.2e-06; C0603
C26, C27, C28, C29, C30, C44, C54, C55: 1e-08; C0402
C31, C45: 1e-05; C1206
C32, C38, C39, C40, C46: 1e-05; C0805
C34: 3.3e-09; C0402
C36, C37: 2.2e-05; C1210
C43: 6.8e-05; 2220
C49: 2.45e-08; R0603
C50: 2.8258362168397e-09; R0603
C51: 7.105e-09; R0603
C52, C53: 0.0001; EXV-9H
F1: 240.0; L0603
I1, I2: 5.2e-06; DR1040
J1: PJ-037B; PJ-037B_PACKAGE
R2, R26, R34: 1000.0; R0603
R7, R8: 4700.0; R0603
R13: 47000.0; R0603
R14, R15, R16, R17, R18, R19, R20, R21, R22, R23, R35, R37, R38, R41, R42, R43: 10000.0; R0603
R24, R32: 100000.0; R0603
R25, R33: 200.0; R0603
R27: 71007.101651032; R0603
R28: 22000.0; R0603
R29: 20000.0; R0603
R30: 150000.0; R0603
R31: 300000.0; R0603
R36: 75000.0; R0603
R39, R40: 95300.0; R0603
R44: 48900.0; R0603
U1: STM32F439IIT6; LQFP176
U2: MAX4995AAUT+T; SOT-23-6
U3: arducam_ov2640; ARDUCAM
U4: IS61WV102416BLL-10MLI
U5: M24M02-DRMN6TP; SOIC-8
U6: 47590-0001; MICRO_USB_AB
U7: prtr5v0u2ax; SOT143B
U8: ASEK-32.768KHz-ECST; ASEK
U9: ASFL1-25MHZ-NCS; ASFL1
U10: idt74fct38072; IDT74FCT38072
U11, U14: LP3878SDX-ADJ/NOPB; WSON-8
U12: tps54225PWP; HTSSOP14
U13: LTC3601EUD#PBF; QFN-16_EP
U15: LTC2928CUHF#PBF; QFN-38_UHF
U16, U17: IRF8306MTRPbF; IRF8306MTRPBF
U18: 4-1437565-2; SW_4-1437565-2
U19: Q65110A2395; LGM67K-G1J2-24-Z
U20, U21: nc7sz125m5x; NC7SZ125M5X

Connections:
CLK_U1_9: U1.9, U8.3
CLK_U1_29: U1.29, U10.6
CLK_U3_8: U3.8, U10.7
CLK_U10_3: U9.3, U10.3
GND: C1.2, C2.2, C3.2, C4.2, C5.2, C6.2, C7.2, C8.2, C9.2, C10.2, C11.2, C12.2, C13.2, C14.2, C15.2, C16.2, C17.2, C18.2, C19.2, C20.2, C21.2, C22.2, C23.2, C24.2, C25.2, C26.2, C27.2, C28.2, C29.2, C30.2, C31.2, C32.2, C33.2, C34.2, C36.2, C37.2, C38.2, C39.2, C40.2, C41.2, C43.1, C43.2, C44.2, C45.2, C46.2, C47.2, C48.2, C49.2, C50.2, C51.2, C52.2, C53.2, C54.2, C55.2, J1.2, R2.2, R13.2, R19.2, R23.2, R26.2, R28.2, R29.2, R31.2, R34.2, R36.2, R39.2, R40.2, R41.2, R42.2, R43.2, U1.14, U1.22, U1.37, U1.61, U1.71, U1.90, U1.102, U1.113, U1.126, U1.135, U1.148, U1.158, U2.2, U3.2, U3.20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
NET_U1_31: R7.1, U1.31, U20.4
NET_U1_39: C19.1, C20.1, F1.1, U1.38, U1.39
NET_U1_48: R17.1, U1.48
NET_U1_58: R16.1, U1.58
NET_U1_125: C22.1, U1.125
NET_U1_166: R15.1, U1.166
NET_U1_171: R14.1, U1.171
NET_U1_176: U18.3, U18.4
NET_U2_3: R13.1, U2.3
NET_U3_19: R8.1, U3.19, U21.4
NET_U4_A2: R21.1, U4.A2
NET_U4_B5: R20.1, U4.B5
NET_U4_G5: R22.1, U4.G5
NET_U5_3: R23.1, U5.3
NET_U11_1: C30.1, U11.1
NET_U11_6: R25.2, R26.1, U11.6
NET_U11_8: R24.1, U11.8
NET_U12_2: R27.2, R28.1, U12.2
NET_U12_3: C33.1, U12.3
NET_U12_4: C34.1, U12.4
NET_U12_10: C35.1, I1.1, U12.10, U12.11
NET_U12_12: C35.2, U12.12
NET_U13_3: C42.2, I2.1, U13.3, U13.4
NET_U13_6: C42.1, U13.6
NET_U13_7: C41.1, U13.7, U13.12
NET_U13_10: R31.1, U13.10
NET_U13_11: R29.1, R30.1, U13.11
NET_U13_ATNET_3: I2.2, R30.2
NET_U14_1: C44.1, U14.1
NET_U14_6: R33.2, R34.1, U14.6
NET_U14_8: R32.1, U14.8
NET_U15_3: R42.1, U15.3
NET_U15_6: R39.1, U15.6
NET_U15_7: R40.1, U15.7
NET_U15_16: R41.1, R44.1, U15.16
NET_U15_18: R38.1, U15.18
NET_U15_19: R37.1, U15.19, U15.20
NET_U15_21: R35.1, R36.1, U15.21, U20.2, U21.2
NET_U15_26: C50.1, U15.26
NET_U15_27: C49.1, U15.27
NET_U15_28: C51.1, U15.28
NET_U15_38: R43.1, U15.38
NET_U16_3: U15.2, U16.3
NET_U17_3: U15.37, U17.3
NET_U18_1: R2.1, U18.1, U18.2
PROC_DCMI_D0: U1.86, U3.18
PROC_DCMI_D1: U1.87, U3.17
PROC_DCMI_D2: U1.88, U3.16
PROC_DCMI_D3: U1.89, U3.15
PROC_DCMI_D4: U1.3, U3.14
PROC_DCMI_D5: U1.145, U3.13
PROC_DCMI_D6: U1.4, U3.12
PROC_DCMI_D7: U1.5, U3.11
PROC_DCMI_D8: U1.83, U3.10
PROC_DCMI_D9: U1.84, U3.9
PROC_DCMI_HSYNC: U1.50, U3.6
PROC_DCMI_PIXCK: U1.52, U3.7
PROC_DCMI_VSYNC: U1.152, U3.5
PROC_FMC_A0: U1.16, U4.A3
PROC_FMC_A1: U1.17, U4.A4
PROC_FMC_A2: U1.18, U4.A5
PROC_FMC_A3: U1.19, U4.B3
PROC_FMC_A4: U1.20, U4.B4
PROC_FMC_A5: U1.21, U4.C3
PROC_FMC_A6: U1.60, U4.C4
PROC_FMC_A7: U1.63, U4.D4
PROC_FMC_A8: U1.64, U4.H2
PROC_FMC_A9: U1.65, U4.H3
PROC_FMC_A10: U1.66, U4.H4
PROC_FMC_A11: U1.67, U4.H5
PROC_FMC_A12: U1.106, U4.G3
PROC_FMC_A13: U1.107, U4.G4
PROC_FMC_A14: U1.108, U4.F3
PROC_FMC_A15: U1.109, U4.F4
PROC_FMC_A16: U1.99, U4.E4
PROC_FMC_A17: U1.100, U4.D3
PROC_FMC_A18: U1.101, U4.H1
PROC_FMC_A19: U1.2, U4.G2
PROC_FMC_D0: U1.104, U4.B6
PROC_FMC_D1: U1.105, U4.C5
PROC_FMC_D2: U1.142, U4.C6
PROC_FMC_D3: U1.143, U4.D5
PROC_FMC_D4: U1.68, U4.E5
PROC_FMC_D5: U1.69, U4.F5
PROC_FMC_D6: U1.70, U4.F6
PROC_FMC_D7: U1.73, U4.G6
PROC_FMC_D8: U1.74, U4.B1
PROC_FMC_D9: U1.75, U4.C1
PROC_FMC_D10: U1.76, U4.C2
PROC_FMC_D11: U1.77, U4.D2
PROC_FMC_D12: U1.78, U4.E2
PROC_FMC_D13: U1.96, U4.F2
PROC_FMC_D14: U1.97, U4.F1
PROC_FMC_D15: U1.98, U4.G1
PROC_FMC_NBL0: U1.169, U4.A1
PROC_GPIO_TO_U1_USB_FAULT: R18.1, U1.7, U2.6
PROC_GPIO_TO_U1_VBUS_EN: R19.1, U1.1, U2.4
PROC_USB_OTG_FS_DM: U6.2, U7.3
PROC_USB_OTG_FS_DP: U6.3, U7.2
PROC_USB_OTG_FS_VBUS: U2.1, U6.1, U7.4
VCC_6V4: C47.1, C48.1, C52.1, C53.1, J1.1, R35.2, R37.2, R38.2, R44.2, U15.11, U15.22, U16.1, U16.2, U16.6, U16.7, U17.1, U17.2, U17.6, U17.7
VCC_S1_6V4: C31.1, C38.1, C39.1, C40.1, R24.2, U11.4, U12.7, U12.13, U12.14, U13.15, U13.16, U16.4, U16.5
VCC_S2_6V4: C45.1, R32.2, U14.4, U17.4, U17.5
VCC_TIER1_1V2: C21.1, C32.1, R25.1, U1.81, U11.5
VCC_TIER1_3V3: C1.1, C2.1, C3.1, C4.1, C5.1, C6.1, C7.1, C8.1, C9.1, C10.1, C11.1, C12.1, C13.1, C14.1, C15.1, C16.1, C17.1, C18.1, C23.1, C24.1, C25.1, C26.1, C27.1, C28.1, C29.1, C36.1, C37.1, C54.1, C55.1, F1.2, I1.2, R7.2, R8.2, R14.2, R15.2, R16.2, R17.2, R18.2, R20.2, R21.2, R22.2, R27.1, U1.6, U1.15, U1.23, U1.36, U1.49, U1.62, U1.72, U1.82, U1.91, U1.103, U1.114, U1.127, U1.136, U1.149, U1.159, U1.172, U3.1, U4.D6, U4.E1, U5.8, U8.4, U9.4, U10.1, U10.2, U12.1, U20.5, U21.5
VCC_TIER1_5V0: C43.2, I2.2, R30.2, U2.5, U13.8
VCC_TIER2_1V2: C46.1, R33.1, U14.5
